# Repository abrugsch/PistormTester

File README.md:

# PiStorm Tester

## Assistance:
If you've gone through the instructions below and watched the video and you need more help decoding what the board is telling you (some things are not so obvious if you're not ultra familiar with the PiStorm schematic) then feel free to hit me up. the best way is usually through Discord via the [PiStorm server](https://discord.gg/mrmyGmvGE5) and I'm @ABrugsch on there too.

## Donate:  
**If you build these, consider [Buying me a coffee](https://ko-fi.com/abrugsch)**
I have spent a considerable amount of time refining the board and the tests that go with them, and will often help people understand what their ZZ9 is telling them. A little coffee goes a long way to helping me keep my sanity 🙂  

### What is?
PiStorm Tester is a PCB that exposes all the IO's of the 68000 DIP64 socket that [PiStorm](https://github.com/captain-amygdala/pistorm/) uses. There are status LED's on all the control/Address/Data Bus lines to easily see if a single line is stuck high or low. Each IO is also broken out to a header for easy connection to an external microcontroller such as an arduino for more accurate analysis of the outputs, or for pulling inputs high or low as required. where the line is either an input or bi-directional (such as the Data bus) the headers have a handy VCC and GND rail adjacent for easy jumpering. 
Combined with testing programs on the pi such as buptest, it becomes easy to narrow down individual faults such as unsoldered or broken individual flip-flops.

### Make Them
* Latest Version gerbers: [RevC.1](https://github.com/abrugsch/PistormTester/tree/main/production/gerbers/PiStormTesterRevC.1.zip)

You can build them by hand. submit the gerbers (Rev C gerbers have adjustments made for ZIF sockets with bigger pins. If you definitely don't want to use a ZIF, a Rev-B board might fit better but RevC should be universal) to a PCB fab of your choice (AllPCB has a free promotion ATM) but then you have to place and solder 60 0603 LED's and 15 4x0402 resistor arrays by hand. That's pretty tedious so I've also included the JLCPCB [production files](https://github.com/abrugsch/PistormTester/tree/main/production) to get them assembled. All the JLC parts are basic parts so it costs barely more to get them assembled than to just order the bare boards. (10x costs around $50 including UK delivery by courier)  
* PistormTester-top-pos-JLC.csv - JLC position file
* PistormTester-BOM-jlc.csv - JLC BOM file
* gerbers/PiStormTesterRevC.1.zip - latest gerber files

~~The big caveat is that they(JLCPCB assembly) don't have a 5v 7-ish MHz oscillator in their assembly catalog so that part has an LCSC part number ([C387338](https://lcsc.com/product-detail/Oscillators_Shenzhen-SCTF-Elec-S3D8-000000A20F30T_C387338.html)) but must be sourced and placed separately.~~ As of RevC.1 there is now a 3.3v oscillator and regulator so that all parts can be assembled by JLC with the included BOM. There are even alternative 3.3v Oscillators if the one in the BOM is out of stock. If you use a RevC or older gerber set, then the BOM and position files will be incorrect so please roll them back to earlier versions.  

__IMPORTANT__ There is now a jumper 0 Ohm resistor in the BOM and position file. If you use the 3.3v regulator and oscillator you ___MUST___ exclude R1 from the build. If you use a 5v Oscillator you ___MUST___ exclude U1, C3 and C4 from the build and keep R1.  

If you do a JLC run of 10 boards, they should come in at around $30 (plus taxes and delivery - Total cost to the UK using an SMD voucher and their cheapest (about 2 weeks) delivery was $37 last time I did a batch, £35 for all red LEDs.)  

The biggest costs in producing these boards are the LED's and the oscillator. If you don't care about colo(u)r of LEDs the cheapest option is to use all red ones as they are significantly cheaper than any other colo(u)r so there is an alternative BOM file with all the LED's using the cheaper RED part. (Although now that the BOM LCSC part numbers have been tweaked to put more expensive ones on places where the lowest quantity are, the difference isn't so great: about $2 between All-Red and different colours.)  
* PistormTester-all-red-BOM-jlc.csv  

### How to
The code folder of this repo has some simple tests for checking that the address and data busses are behaving correctly. Here are the instructions for using them on PiStorm. For more advanced tests, see the note at the bottom of this readme.    

If you have a recent pull of the [main PiStorm repo](https://github.com/captain-amygdala/pistorm/) then you do not need to copy any files as the test files are now included in the PiStorm root folder, though you will still need to follow the build instructions below, but the code files are probably already in your PiStorm folder.  
If not, then copy the files in the [code folder of this repo](https://github.com/abrugsch/PistormTester/tree/main/code) to your pistorm folder on your pi. (put the files in directly, not in a subfolder.)  
Run  
> ```./build_zz9tests.sh```  

to build the test program just like buptest.  
Then run  
> ```sudo ./zz9fulltest```  

* Test 1:  
Watch the LED's on the address bus. they should all light in turn from A1 to A23. AS should dim slightly as it goes from being held high to being pulsed. All data bits should appear to be on for the duration of this test.
* Test 2:  
Watch the Data bus LED's. They should light in turn from D0 through to D15.  
* Test 3:  
**THIS TEST ONLY WORKS FOR NON-A VARIANT FLIP-FLOPS** On A-Variant flip-flops (LVC16373**A** or LVC16374**A**) the data bits won't even appear to light up as they are only on for such a brief period of time  
The zz9fulltest program will then walk the databus lines individually and read the state back so if there is a discrepancy between what is written and what is read then it will be displayed as a data mismatch error.
If you want to force an error, you can go ahead and set one of the data lines high or low with the breakout area by bridging the centre row with an adjacent vcc or gnd. This is probably best done with a ~1K resistor, but not entirely necessary.

Any discrepancies at this point can be referenced to the schematic to find the appropriate pin that might need attention.

For a more thorough test of the data reads there is also zz9readloop which will loop for 2 minutes reading the data bus and displaying the results on screen in Hex and Binary.

simply run  
> ```sudo ./zz9readloop```  

and then modify data bits using the tweak headers and see what comes on the screen. A-variant flip-flops (LVC16373**A** or LVC16374**A**) will hold the data after you set it, allowing you to set multiple bits at a time while only using one wire/resistor to do it.

The program will read at half second intervals for 2 minutes.  
ctrl-c will terminate early  
There is now a video demonstrating the use of the ZZ9 board:  

### Typical problems: 
* Address or data bus LED's don't come on when they are supposed to:  
This usually means the output pin of the flip-flop that should be connected to the CPU pin isn't actually connected. This can either be an incorrectly soldered CPU pin or flip-flop pin. Knowing which Data or Address pin is at fault can then be directly traced through the schematic in the code folder. It can also mean a connection from the CPLD to the flip-flops is broken. This can manifest as both an address pin AND a data pin being out. e.g. A3 and D3, due to the way the internal data path is shared.  
* Address or data LED's stuck on  
can either be a short to VCC or sometimes open circuit on the flip-flops input as the inputs can float high.
* LED's show correct but there's a buptest read mismatch  
Run zz9readloop and while it's doing the loop, put each data pin high or low and see that the program shows the read data correctly (the state of the lights is displayed directly on the read loop in both Hex and Binary (bit) format)  
Example: if you make D3 high (connect to vcc) zz9readloop should say `READ16: read data: 0x0008(hex) 0000000000001000 (binary)`
* Whole 8-bit blocks of any of the address/data busses are not working:  
each 8-bit bank (A1-7, A8-15, A16-24, D0-7, D8-15) is enabled by an output enable pin on the respective latch chip and is controlled by the CPLD. They are active low and if left floating can have unpredictable results, but usually simply fail to operate the entire bank. The OE pins to check for each bank are as follows:  

| bank | chip | pin |  
:-: | :-: | :-:  
| A1-7 | U2 | 1 |  
| A8-15 | U2 | 24 |  
| A16-23 | U6 | 1 |  
| D0-7 | U5 | 1 |  
| D8-15 | U5 | 24 |  

If you need to address any of these issues, here's where to start:  
Data **read** is handled by U3 on the PiStorm  
Data **write** is handled by U5

Address bus (write only) A1-A15 is handled by U2  
Address bus A16-A23 is handled by U6

Reference the [Pistorm schematic](https://github.com/abrugsch/PistormTester/blob/main/code/Pistorm_Rev_B_schematic.pdf) for further details of specific pins to target 

## Advanced tests
Currently the included tests only cover the address and data busses. There are 18 other signal lines that are handled by this tester and at the moment nothing has been written to assess these other lines.  
When viewing the board, in normal operation the following should be lit (dimly as they are being strobed)  
* IPL0
* IPL1
* IPL2
* BG
* VMA
* E
* UDS
* LDS
* RW

This only covers the output of the 384 data buffers, and therefore there could also be hidden disconnections between the 384's and the CPLD.  
Example: a disconnected pin on the 384 on the CPLD side of the RST line meant the CPLD I/O was floating. The test board appeared correct (light off) but in use the emulator wouldn't start because RST was toggling on and off due to floating. Re-flowing the suspect 384 resolved the problem.

Testing of the supporting signals will probably have to be done with a logic analyzer or a complementing microcontroller dev board such as an arduino (one that's 5v tolerant) to read the pins and log what states they take. This board was originally intended to have a socket for a mini/micro arduino but for the sake of flexibility was left off.

As Advanced tests are created by myself or the PiStorm community, they will be documented here. (please submit issues or pull requests for any suitable tests you need or have come up with)

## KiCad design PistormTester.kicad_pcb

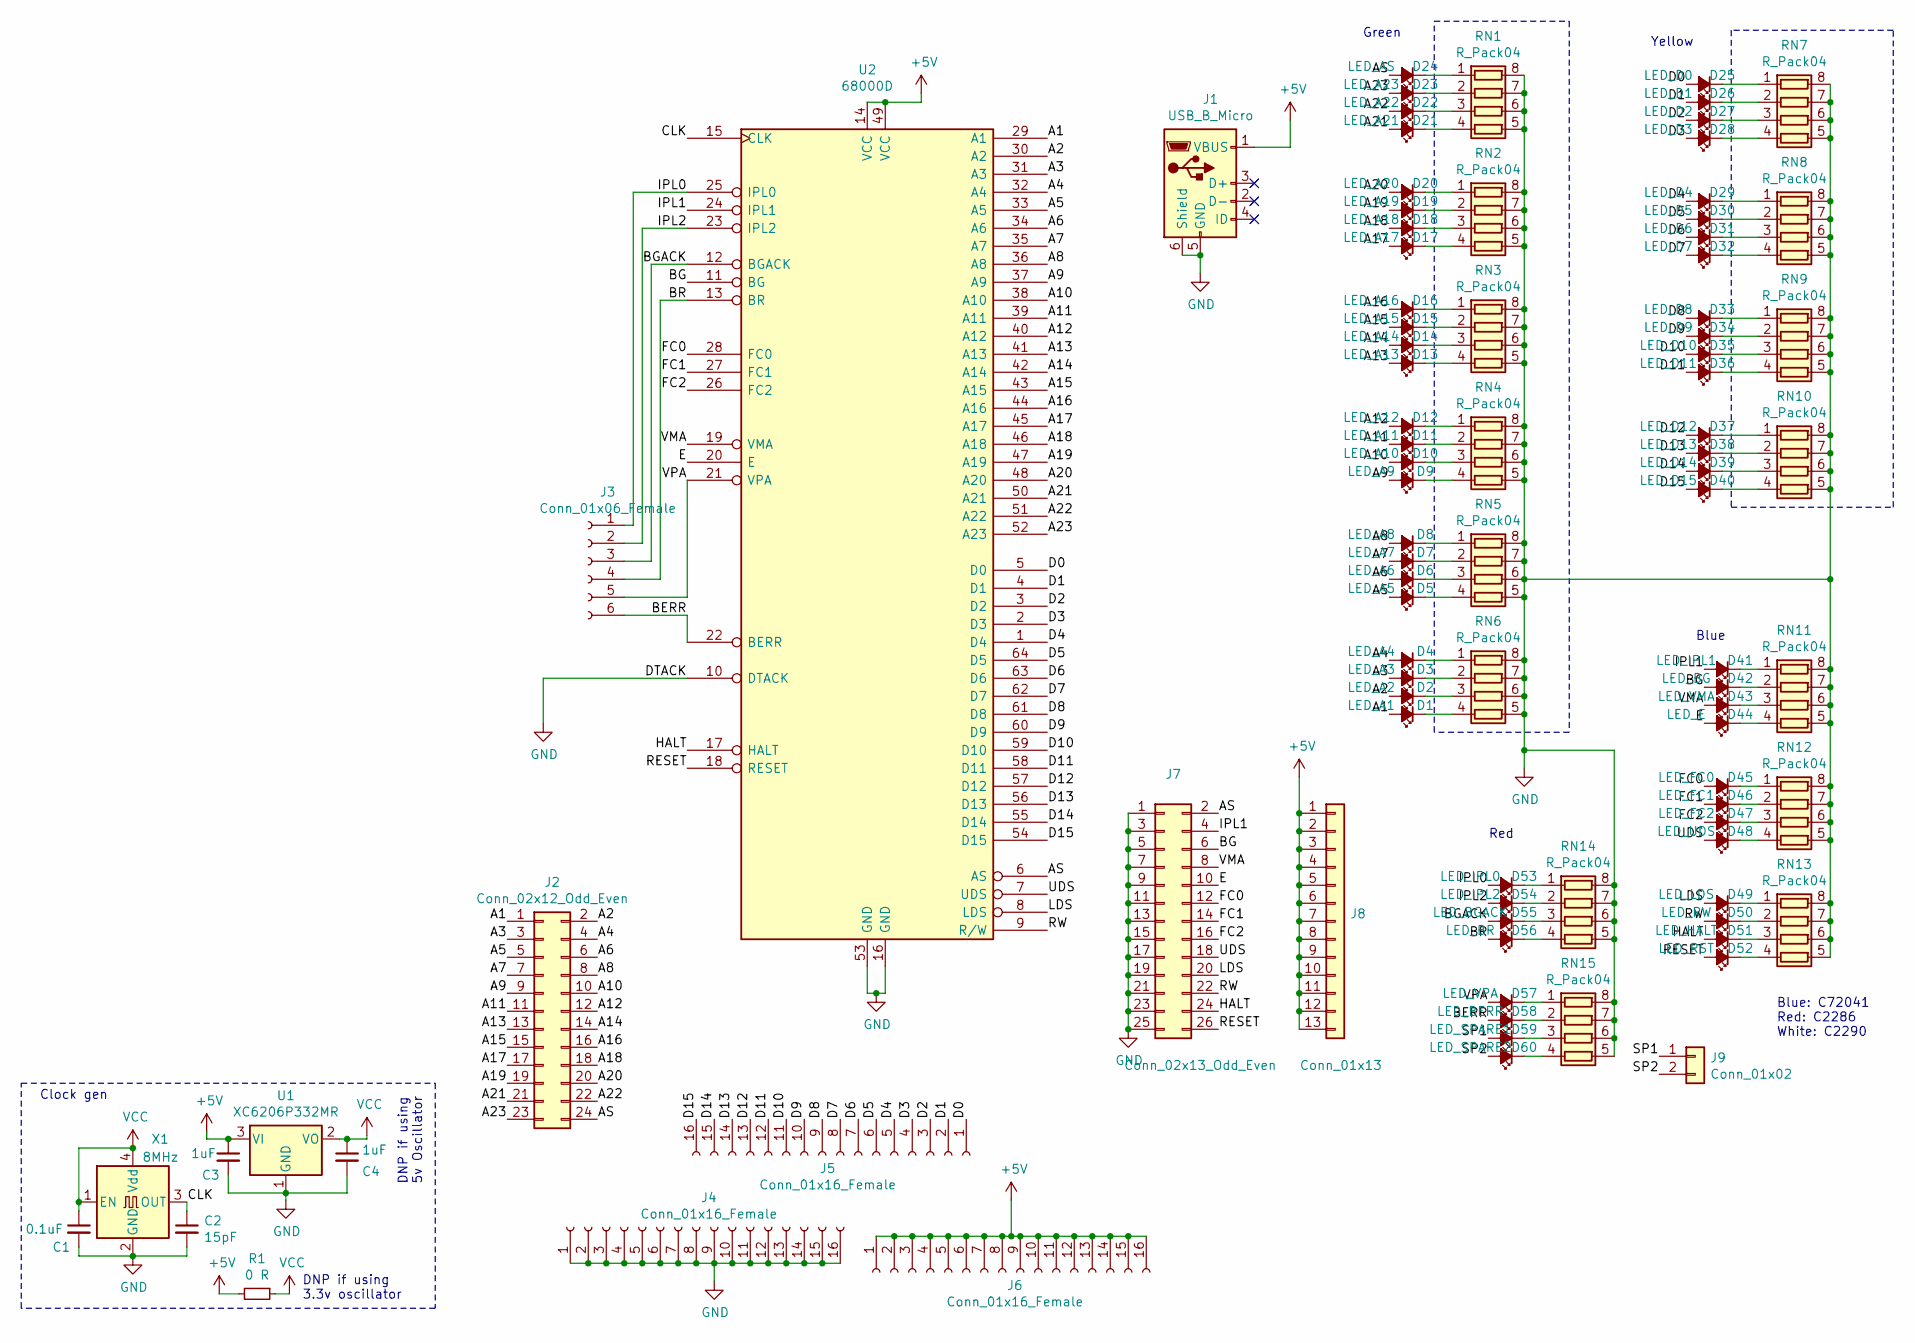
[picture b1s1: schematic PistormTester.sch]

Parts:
C1: 0.1uF; C_0402_1005Metric; LCSC C1525
C2: 15pF; C_0402_1005Metric; LCSC C1548
C3, C4: 1uF; C_0402_1005Metric; LCSC C52923
D1: LED_A1; LED_0603_1608Metric; LCSC C72043
D2: LED_A2; LED_0603_1608Metric; LCSC C72043
D3: LED_A3; LED_0603_1608Metric; LCSC C72043
D4: LED_A4; LED_0603_1608Metric; LCSC C72043
D5: LED_A5; LED_0603_1608Metric; LCSC C72043
D6: LED_A6; LED_0603_1608Metric; LCSC C72043
D7: LED_A7; LED_0603_1608Metric; LCSC C72043
D8: LED_A8; LED_0603_1608Metric; LCSC C72043
D9: LED_A9; LED_0603_1608Metric; LCSC C72043
D10: LED_A10; LED_0603_1608Metric; LCSC C72043
D11: LED_A11; LED_0603_1608Metric; LCSC C72043
D12: LED_A12; LED_0603_1608Metric; LCSC C72043
D13: LED_A13; LED_0603_1608Metric; LCSC C72043
D14: LED_A14; LED_0603_1608Metric; LCSC C72043
D15: LED_A15; LED_0603_1608Metric; LCSC C72043
D16: LED_A16; LED_0603_1608Metric; LCSC C72043
D17: LED_A17; LED_0603_1608Metric; LCSC C72043
D18: LED_A18; LED_0603_1608Metric; LCSC C72043
D19: LED_A19; LED_0603_1608Metric; LCSC C72043
D20: LED_A20; LED_0603_1608Metric; LCSC C72043
D21: LED_A21; LED_0603_1608Metric; LCSC C72043
D22: LED_A22; LED_0603_1608Metric; LCSC C72043
D23: LED_A23; LED_0603_1608Metric; LCSC C72043
D24: LED_AS; LED_0603_1608Metric; LCSC C72043
D25: LED_D0; LED_0603_1608Metric; LCSC C72038
D26: LED_D1; LED_0603_1608Metric; LCSC C72038
D27: LED_D2; LED_0603_1608Metric; LCSC C72038
D28: LED_D3; LED_0603_1608Metric; LCSC C72038
D29: LED_D4; LED_0603_1608Metric; LCSC C72038
D30: LED_D5; LED_0603_1608Metric; LCSC C72038
D31: LED_D6; LED_0603_1608Metric; LCSC C72038
D32: LED_D7; LED_0603_1608Metric; LCSC C72038
D33: LED_D8; LED_0603_1608Metric; LCSC C72038
D34: LED_D9; LED_0603_1608Metric; LCSC C72038
D35: LED_D10; LED_0603_1608Metric; LCSC C72038
D36: LED_D11; LED_0603_1608Metric; LCSC C72038
D37: LED_D12; LED_0603_1608Metric; LCSC C72038
D38: LED_D13; LED_0603_1608Metric; LCSC C72038
D39: LED_D14; LED_0603_1608Metric; LCSC C72038
D40: LED_D15; LED_0603_1608Metric; LCSC C72038
D41: LED_IPL1; LED_0603_1608Metric; LCSC C72041
D42: LED_BG; LED_0603_1608Metric; LCSC C72041
D43: LED_VMA; LED_0603_1608Metric; LCSC C72041
D44: LED_E; LED_0603_1608Metric; LCSC C72041
D45: LED_FC0; LED_0603_1608Metric; LCSC C72041
D46: LED_FC1; LED_0603_1608Metric; LCSC C72041
D47: LED_FC2; LED_0603_1608Metric; LCSC C72038
D48: LED_UDS; LED_0603_1608Metric; LCSC C72041
D49: LED_LDS; LED_0603_1608Metric; LCSC C72041
D50: LED_RW; LED_0603_1608Metric; LCSC C72041
D51: LED_HALT; LED_0603_1608Metric; LCSC C72041
D52: LED_RST; LED_0603_1608Metric; LCSC C72041
D53: LED_IPL0; LED_0603_1608Metric; LCSC C2286
D54: LED_IPL2; LED_0603_1608Metric; LCSC C2286
D55: LED_BGACK; LED_0603_1608Metric; LCSC C2286
D56: LED_BR; LED_0603_1608Metric; LCSC C2286
D57: LED_VPA; LED_0603_1608Metric; LCSC C2286
D58: LED_BERR; LED_0603_1608Metric; LCSC C2286
D59: LED_SPARE1; LED_0603_1608Metric; LCSC C2290
D60: LED_SPARE2; LED_0603_1608Metric; LCSC C2290
J1: USB_B_Micro; micro_usb_U-F-M5SS-W-1; LCSC C145783
J2: Conn_02x12_Odd_Even; PinSocket_2x12_P2.54mm_Vertical
J3: Conn_01x06_Female; PinSocket_1x06_P2.54mm_Vertical
J4, J5, J6: Conn_01x16_Female; PinSocket_1x16_P2.54mm_Vertical
J7: Conn_02x13_Odd_Even; PinSocket_2x13_P2.54mm_Vertical
J8: Conn_01x13; PinSocket_1x13_P2.54mm_Vertical
J9: Conn_01x02; PinSocket_1x02_P2.54mm_Vertical
R1: 0 R; R_0402_1005Metric; LCSC C17168
RN1, RN2, RN3, RN4, RN5, RN6, RN7, RN8, RN9, RN10, RN11, RN12, RN13, RN14, RN15: R_Pack04; R_Array_Concave_4x0402; LCSC C25726
U1: XC6206P332MR; SOT-23; LCSC C5446
U2: 68000D; DIP-64_W22.86mm_Socket_LongPads-big_holes
X1: 8MHz; Oscillator_SMD_EuroQuartz_XO32-4Pin_3.2x2.5mm; LCSC C387336

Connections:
+5V: C3.1, J1.1 (VBUS), J6.1, J6.2, J6.3, J6.4, J6.5, J6.6, J6.7, J6.8, J6.9, J6.10, J6.11, J6.12, J6.13, J6.14, J6.15, J6.16, J8.1, J8.2, J8.3, J8.4, J8.5, J8.6, J8.7, J8.8, J8.9, J8.10, J8.11, J8.12, J8.13, R1.2, U1.3 (VI), U2.14 (VCC), U2.49 (VCC)
/A1: D1.2 (A), J2.1, U2.29 (A1)
/A2: D2.2 (A), J2.2, U2.30 (A2)
/A3: D3.2 (A), J2.3, U2.31 (A3)
/A4: D4.2 (A), J2.4, U2.32 (A4)
/A5: D5.2 (A), J2.5, U2.33 (A5)
/A6: D6.2 (A), J2.6, U2.34 (A6)
/A7: D7.2 (A), J2.7, U2.35 (A7)
/A8: D8.2 (A), J2.8, U2.36 (A8)
/A9: D9.2 (A), J2.9, U2.37 (A9)
/A10: D10.2 (A), J2.10, U2.38 (A10)
/A11: D11.2 (A), J2.11, U2.39 (A11)
/A12: D12.2 (A), J2.12, U2.40 (A12)
/A13: D13.2 (A), J2.13, U2.41 (A13)
/A14: D14.2 (A), J2.14, U2.42 (A14)
/A15: D15.2 (A), J2.15, U2.43 (A15)
/A16: D16.2 (A), J2.16, U2.44 (A16)
/A17: D17.2 (A), J2.17, U2.45 (A17)
/A18: D18.2 (A), J2.18, U2.46 (A18)
/A19: D19.2 (A), J2.19, U2.47 (A19)
/A20: D20.2 (A), J2.20, U2.48 (A20)
/A21: D21.2 (A), J2.21, U2.50 (A21)
/A22: D22.2 (A), J2.22, U2.51 (A22)
/A23: D23.2 (A), J2.23, U2.52 (A23)
/AS: D24.2 (A), J2.24, J7.2, U2.6 (AS)
/BERR: D58.2 (A), J3.6, U2.22 (BERR)
/BG: D42.2 (A), J7.6, U2.11 (BG)
/BGACK: D55.2 (A), J3.3, U2.12 (BGACK)
/BR: D56.2 (A), J3.4, U2.13 (BR)
/CLK: C2.1, U2.15 (CLK), X1.3 (OUT)
/D0: D25.2 (A), J5.1, U2.5 (D0)
/D1: D26.2 (A), J5.2, U2.4 (D1)
/D2: D27.2 (A), J5.3, U2.3 (D2)
/D3: D28.2 (A), J5.4, U2.2 (D3)
/D4: D29.2 (A), J5.5, U2.1 (D4)
/D5: D30.2 (A), J5.6, U2.64 (D5)
/D6: D31.2 (A), J5.7, U2.63 (D6)
/D7: D32.2 (A), J5.8, U2.62 (D7)
/D8: D33.2 (A), J5.9, U2.61 (D8)
/D9: D34.2 (A), J5.10, U2.60 (D9)
/D10: D35.2 (A), J5.11, U2.59 (D10)
/D11: D36.2 (A), J5.12, U2.58 (D11)
/D12: D37.2 (A), J5.13, U2.57 (D12)
/D13: D38.2 (A), J5.14, U2.56 (D13)
/D14: D39.2 (A), J5.15, U2.55 (D14)
/D15: D40.2 (A), J5.16, U2.54 (D15)
/E: D44.2 (A), J7.10, U2.20 (E)
/FC0: D45.2 (A), J7.12, U2.28 (FC0)
/FC1: D46.2 (A), J7.14, U2.27 (FC1)
/FC2: D47.2 (A), J7.16, U2.26 (FC2)
/HALT: D51.2 (A), J7.24, U2.17 (HALT)
/IPL0: D53.2 (A), J3.1, U2.25 (IPL0)
/IPL1: D41.2 (A), J7.4, U2.24 (IPL1)
/IPL2: D54.2 (A), J3.2, U2.23 (IPL2)
/LDS: D49.2 (A), J7.20, U2.8 (LDS)
/RESET: D52.2 (A), J7.26, U2.18 (RESET)
/RW: D50.2 (A), J7.22, U2.9 (R/W)
/SP1: D59.2 (A), J9.1
/SP2: D60.2 (A), J9.2
/UDS: D48.2 (A), J7.18, U2.7 (UDS)
/VMA: D43.2 (A), J7.8, U2.19 (VMA)
/VPA: D57.2 (A), J3.5, U2.21 (VPA)
GND: C1.2, C2.2, C3.2, C4.2, J1.5 (GND), J1.6 (Shield), J4.1, J4.2, J4.3, J4.4, J4.5, J4.6, J4.7, J4.8, J4.9, J4.10, J4.11, J4.12, J4.13, J4.14, J4.15, J4.16, J7.1, J7.3, J7.5, J7.7, J7.9, J7.11, J7.13, J7.15, J7.17, J7.19, J7.21, J7.23, J7.25, RN1.5 (R4.2), RN1.6 (R3.2), RN1.7 (R2.2), RN1.8 (R1.2), RN2.5 (R4.2), RN2.6 (R3.2), RN2.7 (R2.2), RN2.8 (R1.2), RN3.5 (R4.2), RN3.6 (R3.2), RN3.7 (R2.2), RN3.8 (R1.2), RN4.5 (R4.2), RN4.6 (R3.2), RN4.7 (R2.2), RN4.8 (R1.2), RN5.5 (R4.2), RN5.6 (R3.2), RN5.7 (R2.2), RN5.8 (R1.2), RN6.5 (R4.2), RN6.6 (R3.2), RN6.7 (R2.2), RN6.8 (R1.2), RN7.5 (R4.2), RN7.6 (R3.2), RN7.7 (R2.2), RN7.8 (R1.2), RN8.5 (R4.2), RN8.6 (R3.2), RN8.7 (R2.2), RN8.8 (R1.2), RN9.5 (R4.2), RN9.6 (R3.2), RN9.7 (R2.2), RN9.8 (R1.2), RN10.5 (R4.2), RN10.6 (R3.2), RN10.7 (R2.2), RN10.8 (R1.2), RN11.5 (R4.2), RN11.6 (R3.2), RN11.7 (R2.2), RN11.8 (R1.2), RN12.5 (R4.2), RN12.6 (R3.2), RN12.7 (R2.2), RN12.8 (R1.2), RN13.5 (R4.2), RN13.6 (R3.2), RN13.7 (R2.2), RN13.8 (R1.2), RN14.5 (R4.2), RN14.6 (R3.2), RN14.7 (R2.2), RN14.8 (R1.2), RN15.5 (R4.2), RN15.6 (R3.2), RN15.7 (R2.2), RN15.8 (R1.2), U1.1 (GND), U2.10 (DTACK), U2.16 (GND), U2.53 (GND), X1.2 (GND)
unnamed: D1.1 (K), RN6.4 (R4.1)
unnamed: D2.1 (K), RN6.3 (R3.1)
unnamed: D3.1 (K), RN6.2 (R2.1)
unnamed: D4.1 (K), RN6.1 (R1.1)
unnamed: D5.1 (K), RN5.4 (R4.1)
unnamed: D6.1 (K), RN5.3 (R3.1)
unnamed: D7.1 (K), RN5.2 (R2.1)
unnamed: D8.1 (K), RN5.1 (R1.1)
unnamed: D9.1 (K), RN4.4 (R4.1)
unnamed: D10.1 (K), RN4.3 (R3.1)
unnamed: D11.1 (K), RN4.2 (R2.1)
unnamed: D12.1 (K), RN4.1 (R1.1)
unnamed: D13.1 (K), RN3.4 (R4.1)
unnamed: D14.1 (K), RN3.3 (R3.1)
unnamed: D15.1 (K), RN3.2 (R2.1)
unnamed: D16.1 (K), RN3.1 (R1.1)
unnamed: D17.1 (K), RN2.4 (R4.1)
unnamed: D18.1 (K), RN2.3 (R3.1)
unnamed: D19.1 (K), RN2.2 (R2.1)
unnamed: D20.1 (K), RN2.1 (R1.1)
unnamed: D21.1 (K), RN1.4 (R4.1)
unnamed: D22.1 (K), RN1.3 (R3.1)
unnamed: D23.1 (K), RN1.2 (R2.1)
unnamed: D24.1 (K), RN1.1 (R1.1)
unnamed: D25.1 (K), RN7.1 (R1.1)
unnamed: D26.1 (K), RN7.2 (R2.1)
unnamed: D27.1 (K), RN7.3 (R3.1)
unnamed: D28.1 (K), RN7.4 (R4.1)
unnamed: D29.1 (K), RN8.1 (R1.1)
unnamed: D30.1 (K), RN8.2 (R2.1)
unnamed: D31.1 (K), RN8.3 (R3.1)
unnamed: D32.1 (K), RN8.4 (R4.1)
unnamed: D33.1 (K), RN9.1 (R1.1)
unnamed: D34.1 (K), RN9.2 (R2.1)
unnamed: D35.1 (K), RN9.3 (R3.1)
unnamed: D36.1 (K), RN9.4 (R4.1)
unnamed: D37.1 (K), RN10.1 (R1.1)
unnamed: D38.1 (K), RN10.2 (R2.1)
unnamed: D39.1 (K), RN10.3 (R3.1)
unnamed: D40.1 (K), RN10.4 (R4.1)
unnamed: D41.1 (K), RN11.1 (R1.1)
unnamed: D42.1 (K), RN11.2 (R2.1)
unnamed: D43.1 (K), RN11.3 (R3.1)
unnamed: D44.1 (K), RN11.4 (R4.1)
unnamed: D45.1 (K), RN12.1 (R1.1)
unnamed: D46.1 (K), RN12.2 (R2.1)
unnamed: D47.1 (K), RN12.3 (R3.1)
unnamed: D48.1 (K), RN12.4 (R4.1)
unnamed: D49.1 (K), RN13.1 (R1.1)
unnamed: D50.1 (K), RN13.2 (R2.1)
unnamed: D51.1 (K), RN13.3 (R3.1)
unnamed: D52.1 (K), RN13.4 (R4.1)
unnamed: D53.1 (K), RN14.1 (R1.1)
unnamed: D54.1 (K), RN14.2 (R2.1)
unnamed: D55.1 (K), RN14.3 (R3.1)
unnamed: D56.1 (K), RN14.4 (R4.1)
unnamed: D57.1 (K), RN15.1 (R1.1)
unnamed: D58.1 (K), RN15.2 (R2.1)
unnamed: D59.1 (K), RN15.3 (R3.1)
unnamed: D60.1 (K), RN15.4 (R4.1)
VCC: C1.1, C4.1, R1.1, U1.2 (VO), X1.1 (EN), X1.4 (Vdd)

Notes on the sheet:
Clock gen
Green
Yellow
Blue: C72041 Red: C2286 White: C2290
Blue
Red
DNP if using 3.3v oscillator
DNP if using 5v Oscillator

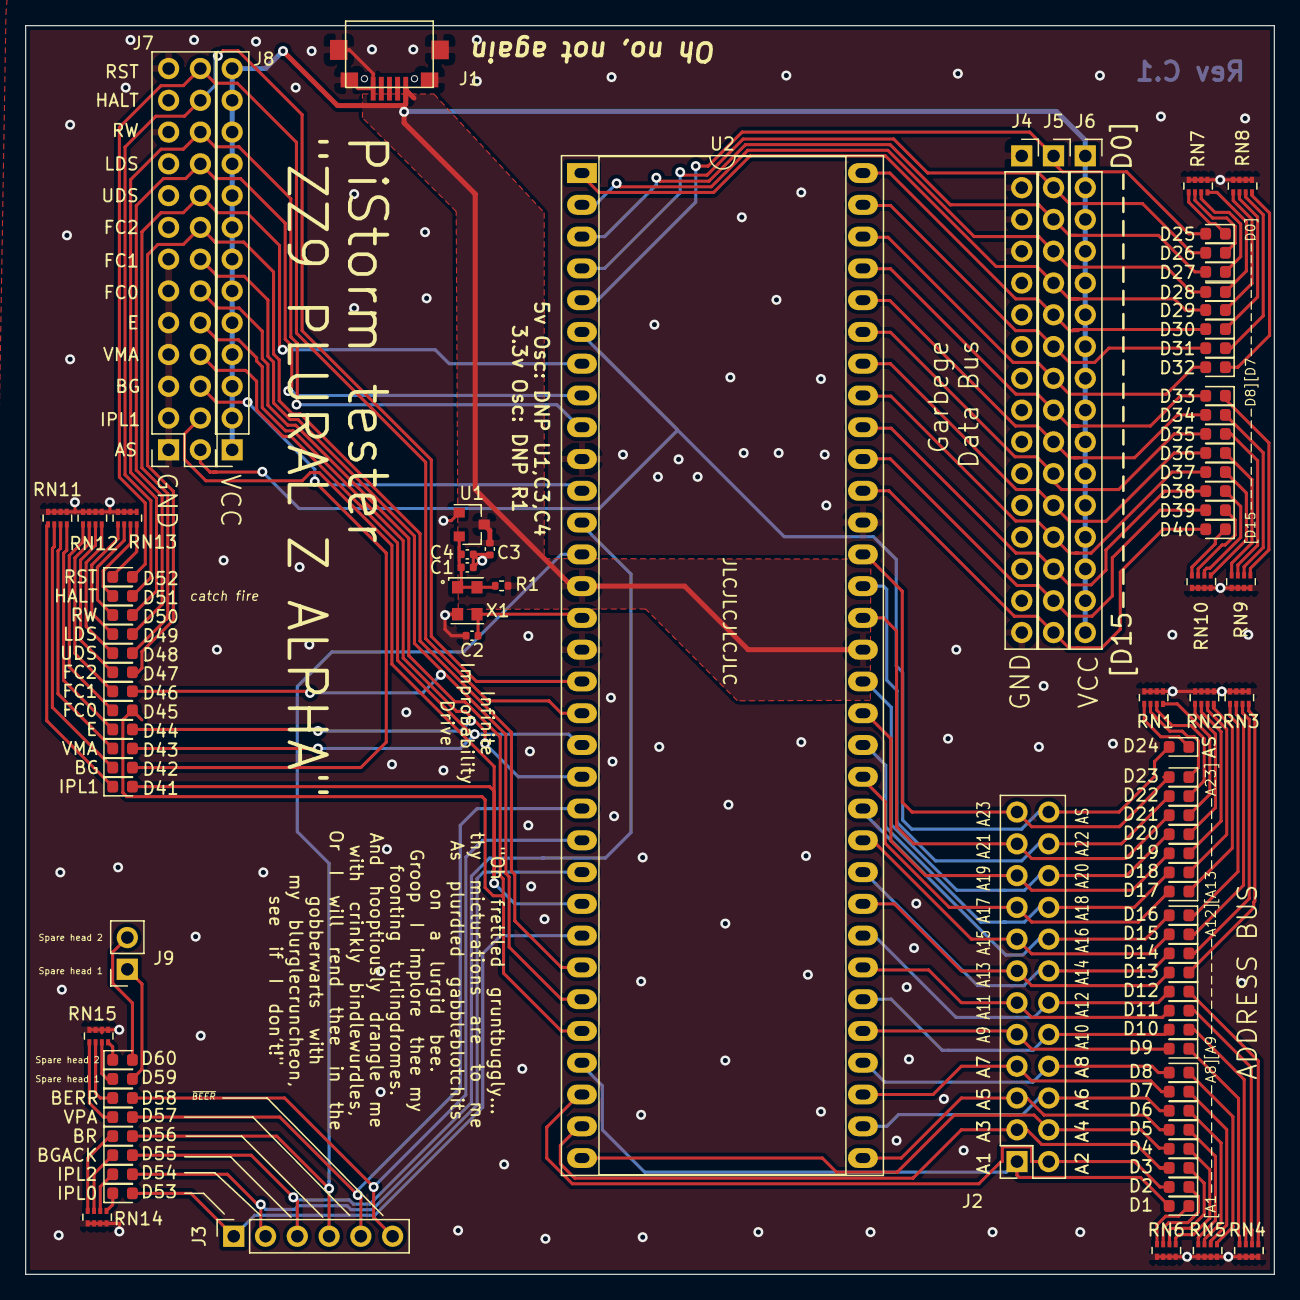
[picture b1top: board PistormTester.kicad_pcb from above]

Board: 2 copper layers, 99.8 x 99.8 mm, 92 parts (0 on the bottom side), 124 nets.

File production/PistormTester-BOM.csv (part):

"Source:","C:\Users\al\Documents\Kicad projects\PistormTester\PistormTester.sch"
"Date:","19/08/2021 20:47:15"
"Tool:","Eeschema (5.1.10)-1"
"Generator:","C:\Program Files\KiCad\bin\scripting\plugins/bom_csv_grouped_by_value.py"
"Component Count:","92"

"Individual Components:"

"Item","Qty","Reference(s)","Value","LibPart","Footprint","Datasheet","LCSC"
"","","C1","0.1uF","Device:C_Small","Capacitor_SMD:C_0402_1005Metric","~","C1525"
"","","C2","15pF","Device:C_Small","Capacitor_SMD:C_0402_1005Metric","~","C1548"
"","","C3","1uF","Device:C_Small","Capacitor_SMD:C_0402_1005Metric","~","C52923"
"","","C4","1uF","Device:C_Small","Capacitor_SMD:C_0402_1005Metric","~","C52923"
"","","D1","LED_A1","Device:LED_Small_ALT","LED_SMD:LED_0603_1608Metric","~","C72043"
"","","D2","LED_A2","Device:LED_Small_ALT","LED_SMD:LED_0603_1608Metric","~","C72043"
"","","D3","LED_A3","Device:LED_Small_ALT","LED_SMD:LED_0603_1608Metric","~","C72043"
"","","D4","LED_A4","Device:LED_Small_ALT","LED_SMD:LED_0603_1608Metric","~","C72043"
"","","D5","LED_A5","Device:LED_Small_ALT","LED_SMD:LED_0603_1608Metric","~","C72043"
"","","D6","LED_A6","Device:LED_Small_ALT","LED_SMD:LED_0603_1608Metric","~","C72043"
"","","D7","LED_A7","Device:LED_Small_ALT","LED_SMD:LED_0603_1608Metric","~","C72043"
"","","D8","LED_A8","Device:LED_Small_ALT","LED_SMD:LED_0603_1608Metric","~","C72043"
"","","D9","LED_A9","Device:LED_Small_ALT","LED_SMD:LED_0603_1608Metric","~","C72043"
"","","D10","LED_A10","Device:LED_Small_ALT","LED_SMD:LED_0603_1608Metric","~","C72043"
"","","D11","LED_A11","Device:LED_Small_ALT","LED_SMD:LED_0603_1608Metric","~","C72043"
"","","D12","LED_A12","Device:LED_Small_ALT","LED_SMD:LED_0603_1608Metric","~","C72043"
"","","D13","LED_A13","Device:LED_Small_ALT","LED_SMD:LED_0603_1608Metric","~","C72043"
"","","D14","LED_A14","Device:LED_Small_ALT","LED_SMD:LED_0603_1608Metric","~","C72043"
"","","D15","LED_A15","Device:LED_Small_ALT","LED_SMD:LED_0603_1608Metric","~","C72043"
"","","D16","LED_A16","Device:LED_Small_ALT","LED_SMD:LED_0603_1608Metric","~","C72043"
"","","D17","LED_A17","Device:LED_Small_ALT","LED_SMD:LED_0603_1608Metric","~","C72043"
"","","D18","LED_A18","Device:LED_Small_ALT","LED_SMD:LED_0603_1608Metric","~","C72043"
"","","D19","LED_A19","Device:LED_Small_ALT","LED_SMD:LED_0603_1608Metric","~","C72043"
"","","D20","LED_A20","Device:LED_Small_ALT","LED_SMD:LED_0603_1608Metric","~","C72043"
"","","D21","LED_A21","Device:LED_Small_ALT","LED_SMD:LED_0603_1608Metric","~","C72043"
"","","D22","LED_A22","Device:LED_Small_ALT","LED_SMD:LED_0603_1608Metric","~","C72043"
"","","D23","LED_A23","Device:LED_Small_ALT","LED_SMD:LED_0603_1608Metric","~","C72043"
"","","D24","LED_AS","Device:LED_Small_ALT","LED_SMD:LED_0603_1608Metric","~","C72043"
"","","D25","LED_D0","Device:LED_Small_ALT","LED_SMD:LED_0603_1608Metric","~","C72038"
"","","D26","LED_D1","Device:LED_Small_ALT","LED_SMD:LED_0603_1608Metric","~","C72038"
"","","D27","LED_D2","Device:LED_Small_ALT","LED_SMD:LED_0603_1608Metric","~","C72038"
"","","D28","LED_D3","Device:LED_Small_ALT","LED_SMD:LED_0603_1608Metric","~","C72038"
"","","D29","LED_D4","Device:LED_Small_ALT","LED_SMD:LED_0603_1608Metric","~","C72038"
"","","D30","LED_D5","Device:LED_Small_ALT","LED_SMD:LED_0603_1608Metric","~","C72038"
"","","D31","LED_D6","Device:LED_Small_ALT","LED_SMD:LED_0603_1608Metric","~","C72038"
"","","D32","LED_D7","Device:LED_Small_ALT","LED_SMD:LED_0603_1608Metric","~","C72038"
"","","D33","LED_D8","Device:LED_Small_ALT","LED_SMD:LED_0603_1608Metric","~","C72038"
"","","D34","LED_D9","Device:LED_Small_ALT","LED_SMD:LED_0603_1608Metric","~","C72038"
"","","D35","LED_D10","Device:LED_Small_ALT","LED_SMD:LED_0603_1608Metric","~","C72038"
"","","D36","LED_D11","Device:LED_Small_ALT","LED_SMD:LED_0603_1608Metric","~","C72038"
"","","D37","LED_D12","Device:LED_Small_ALT","LED_SMD:LED_0603_1608Metric","~","C72038"
"","","D38","LED_D13","Device:LED_Small_ALT","LED_SMD:LED_0603_1608Metric","~","C72038"
"","","D39","LED_D14","Device:LED_Small_ALT","LED_SMD:LED_0603_1608Metric","~","C72038"
"","","D40","LED_D15","Device:LED_Small_ALT","LED_SMD:LED_0603_1608Metric","~","C72038"
"","","D41","LED_IPL1","Device:LED_Small_ALT","LED_SMD:LED_0603_1608Metric","~","C72041"
"","","D42","LED_BG","Device:LED_Small_ALT","LED_SMD:LED_0603_1608Metric","~","C72041"
"","","D43","LED_VMA","Device:LED_Small_ALT","LED_SMD:LED_0603_1608Metric","~","C72041"
"","","D44","LED_E","Device:LED_Small_ALT","LED_SMD:LED_0603_1608Metric","~","C72041"
"","","D45","LED_FC0","Device:LED_Small_ALT","LED_SMD:LED_0603_1608Metric","~","C72041"
"","","D46","LED_FC1","Device:LED_Small_ALT","LED_SMD:LED_0603_1608Metric","~","C72041"
"","","D47","LED_FC2","Device:LED_Small_ALT","LED_SMD:LED_0603_1608Metric","~","C72038"
"","","D48","LED_UDS","Device:LED_Small_ALT","LED_SMD:LED_0603_1608Metric","~","C72041"
"","","D49","LED_LDS","Device:LED_Small_ALT","LED_SMD:LED_0603_1608Metric","~","C72041"
"","","D50","LED_RW","Device:LED_Small_ALT","LED_SMD:LED_0603_1608Metric","~","C72041"
"","","D51","LED_HALT","Device:LED_Small_ALT","LED_SMD:LED_0603_1608Metric","~","C72041"
"","","D52","LED_RST","Device:LED_Small_ALT","LED_SMD:LED_0603_1608Metric","~","C72041"
"","","D53","LED_IPL0","Device:LED_Small_ALT","LED_SMD:LED_0603_1608Metric","~","C2286"
"","","D54","LED_IPL2","Device:LED_Small_ALT","LED_SMD:LED_0603_1608Metric","~","C2286"
"","","D55","LED_BGACK","Device:LED_Small_ALT","LED_SMD:LED_0603_1608Metric","~","C2286"
"","","D56","LED_BR","Device:LED_Small_ALT","LED_SMD:LED_0603_1608Metric","~","C2286"
"","","D57","LED_VPA","Device:LED_Small_ALT","LED_SMD:LED_0603_1608Metric","~","C2286"
"","","D58","LED_BERR","Device:LED_Small_ALT","LED_SMD:LED_0603_1608Metric","~","C2286"
"","","D59","LED_SPARE1","Device:LED_Small_ALT","LED_SMD:LED_0603_1608Metric","~","C2290"
"","","D60","LED_SPARE2","Device:LED_Small_ALT","LED_SMD:LED_0603_1608Metric","~","C2290"
"","","J1","USB_B_Micro","Connector:USB_B_Micro","My_parts:micro_usb_U-F-M5SS-W-1","~","C145783"
"","","J2","Conn_02x12_Odd_Even","Connector_Generic:Conn_02x12_Odd_Even","Connector_PinSocket_2.54mm:PinSocket_2x12_P2.54mm_Vertical","~",""
"","","J3","Conn_01x06_Female","Connector:Conn_01x06_Female","Connector_PinSocket_2.54mm:PinSocket_1x06_P2.54mm_Vertical","~",""
"","","J4","Conn_01x16_Female","Connector:Conn_01x16_Female","Connector_PinSocket_2.54mm:PinSocket_1x16_P2.54mm_Vertical","~",""
"","","J5","Conn_01x16_Female","Connector:Conn_01x16_Female","Connector_PinSocket_2.54mm:PinSocket_1x16_P2.54mm_Vertical","~",""
"","","J6","Conn_01x16_Female","Connector:Conn_01x16_Female","Connector_PinSocket_2.54mm:PinSocket_1x16_P2.54mm_Vertical","~",""
"","","J7","Conn_02x13_Odd_Even","Connector_Generic:Conn_02x13_Odd_Even","Connector_PinSocket_2.54mm:PinSocket_2x13_P2.54mm_Vertical","~",""
"","","J8","Conn_01x13","Connector_Generic:Conn_01x13","Connector_PinSocket_2.54mm:PinSocket_1x13_P2.54mm_Vertical","~",""
"","","J9","Conn_01x02","Connector_Generic:Conn_01x02","Connector_PinSocket_2.54mm:PinSocket_1x02_P2.54mm_Vertical","~",""
"","","R1","0 R","Device:R_Small","Resistor_SMD:R_0402_1005Metric","~","C17168"
"","","RN1","R_Pack04","Device:R_Pack04","Resistor_SMD:R_Array_Concave_4x0402","~","C25726"
"","","RN2","R_Pack04","Device:R_Pack04","Resistor_SMD:R_Array_Concave_4x0402","~","C25726"
"","","RN3","R_Pack04","Device:R_Pack04","Resistor_SMD:R_Array_Concave_4x0402","~","C25726"
"","","RN4","R_Pack04","Device:R_Pack04","Resistor_SMD:R_Array_Concave_4x0402","~","C25726"
"","","RN5","R_Pack04","Device:R_Pack04","Resistor_SMD:R_Array_Concave_4x0402","~","C25726"
"","","RN6","R_Pack04","Device:R_Pack04","Resistor_SMD:R_Array_Concave_4x0402","~","C25726"
"","","RN7","R_Pack04","Device:R_Pack04","Resistor_SMD:R_Array_Concave_4x0402","~","C25726"
"","","RN8","R_Pack04","Device:R_Pack04","Resistor_SMD:R_Array_Concave_4x0402","~","C25726"
"","","RN9","R_Pack04","Device:R_Pack04","Resistor_SMD:R_Array_Concave_4x0402","~","C25726"
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
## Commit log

2021-06-19 Rev A
    Initial REV A commit. board is designed and fettled but needs production files making
2021-06-21 initial checkin
    Rev A as sent to JLC on 19/06/21
2021-06-21 first major version of readme
    TBD. add some pics and board renders
2021-06-21 added caveat
2021-06-21 add pics
2021-06-21 moved to correct subfolder
2021-06-21 added hero image
2021-06-25 Rev B tweaks to layout
    cleaned up front pours and track routes
2021-07-06 added tester code
    minor updates to Rev B of the PCB, added ZZ9fulltest testing code to run on the pi. updated howto instructions.
2021-07-06 formatting
2021-07-06 more formatting
2021-07-06 assembly instructions
2021-07-06 Updated gerbers to REV B
2021-07-06 Rev B warning!
2021-07-14 added read loop test
2021-07-14 Updated test usage instructions for new tests
2021-07-15 increased databus tests
    increased duration of databus walk tests to go in both directions to catch potential D15 errors
2021-07-15 Updated readme.md
    added reference to the PiStorm project
2021-07-16 updated gerber zips
    made more specific versions of the gerber zip files
2021-07-16 fixed PCB outline wonk. updated to Rev C
    Rev B has been sent to production to further changes are now Rev C
2021-07-22 readme update
2021-07-23 changed crop for github social preview wotsit
2021-08-09 Update of readme.md
    added HOWTO video and note about test files in the main repo
2021-08-09 Update README.md
    updated testing procedure with zz9readloop
2021-08-19 REV C - Fixed ZIF holes
    Made the holes for the 68K socket significantly bigger (and moved slightly inboard) to better accommodate ZIF sockets with silly big pins.
    minor re-routing of a few signals too.
2021-08-19 Added RevC gerbers
2021-08-19 updated readme to RevC
2021-08-19 Change to a 3.3v oscillator RevC.1
    switched to a 3.3v Oscillator and an associated 3.3v regulator
2021-08-19 tweaks to production files
2021-08-19 Update README.md
    updated for RevC.1
2021-08-19 Update README.md
    added text about DNP'ing R1
2021-08-23 Update PistormTester-top-pos-JLC.csv
    rotate J1 180 deg
2021-08-24 Update README.md
    added Ko-Fi link
2021-10-03 updated "All Red BOM" to actually be all red.
    made the previous "All Red" to be "All White" as an additional BOM
2021-10-03 Update PistormTester-all-red-BOM-jlc.csv
    fixed ID10T error in previous checkin
2022-01-19 Update README.md
    added additional typical problem
